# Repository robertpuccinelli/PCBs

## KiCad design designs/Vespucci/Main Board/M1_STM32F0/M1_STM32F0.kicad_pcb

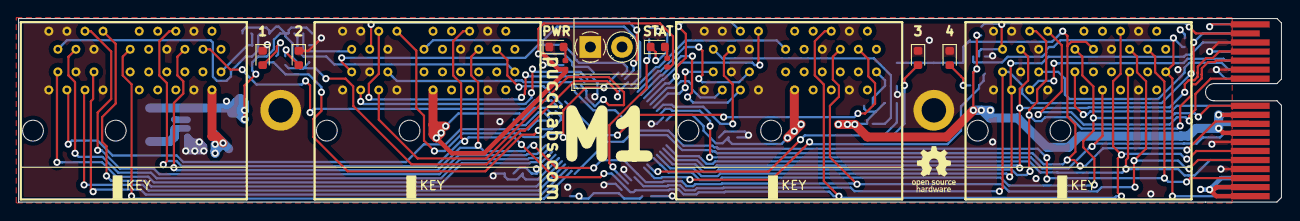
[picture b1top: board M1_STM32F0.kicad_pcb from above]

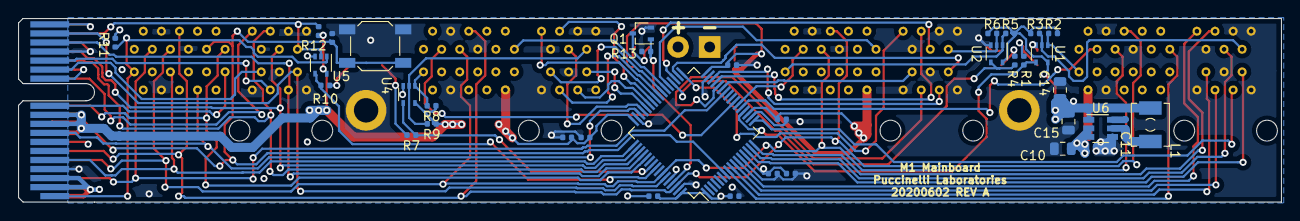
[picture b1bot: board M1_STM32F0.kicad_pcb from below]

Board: 4 copper layers, 139.7 x 20.3 mm, 52 parts (35 on the bottom side), 67 nets.

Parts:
C1, C3, C4, C5, C6, C7, C9, C11: 100nF; C_0402_1005Metric
C2, C8: 4.7uF; C_0402_1005Metric
C10: 4.7uF; C_0805_2012Metric
C14, C15: 22uF; C_0805_2012Metric
D1, D2, D3, D4, D5, D6: LED; LED_0603_1608Metric
G1: OSHW_logo
H1, H2: MountingHole_Pad; MountingHole_2.7mm_M2.5_ISO7380_Pad
J1, J2, J3, J5: PCIe Connector; UMAX_3091-10100T_PCIe_x1
J6: PCIe Card Edge; BUS_PCIexpress_x1
J7: Screw_Terminal_01x02; TerminalBlock_Phoenix_PT-1,5-2-3.5-H_1x02_P3.50mm_Horizontal
L1: 3.3uH; MS0420
Q1: BSS138W; SOT-323_SC-70
R1, R4, R7, R10, R14, R15: 470R; R_0402_1005Metric
R2, R3, R5, R6, R8, R9, R11, R12: 9K53; R_0402_1005Metric
R13: 51K; R_0402_1005Metric
SW1: SW_Push; SW_SPST_SKQG_WithoutStem
U1, U2, U4, U5: NL17SZ00; SOT-353_SC-70-5
U3: STM32F070RBTx; LQFP-64_10x10mm_P0.5mm
U6: AP6320x; TSOT-23-6

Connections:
+BATT: C10.1, J1.a2, J1.a3, J1.b1, J1.b2, J2.a2, J2.a3, J2.b1, J2.b2, J3.a2, J3.a3, J3.b1, J3.b2, J5.a2, J5.a3, J5.b1, J5.b2, J6.a2, J6.a3, J6.b1, J6.b2, J7.1, U6.2, U6.3
/ADC_IN5: J1.b3, U3.21
/ADC_IN6: J2.b3, U3.22
/ADC_IN7: J3.b3, U3.23
/ADC_IN8: J5.b3, J6.b3, U3.26
/I2C1_SCL: J1.b5, J2.b5, J3.b5, J5.b5, J6.b5, U3.58
/I2C1_SDA: J1.b6, J2.b6, J3.b6, J5.b6, J6.b6, U3.62
/PRSNT1: R1.1, U1.4, U3.20
/PRSNT1A: J1.a1, R2.2, U1.1
/PRSNT1B: J1.b17, R3.2, U1.2
/PRSNT2: R4.1, U2.4, U3.36
/PRSNT2A: J2.a1, R5.2, U2.1
/PRSNT2B: J2.b17, R6.2, U2.2
/PRSNT3: R7.1, U3.55, U4.4
/PRSNT3A: J3.a1, R8.2, U4.1
/PRSNT3B: J3.b17, R9.2, U4.2
/PRSNT4: R10.1, U3.56, U5.4
/PRSNT4A: J5.a1, J6.a1, R11.2, U5.1
/PRSNT4B: J5.b17, J6.b17, R12.2, U5.2
/PWROK4: J5.a11, J6.a11
/RST: C1.1, J5.b9, J6.b9, SW1.2, U3.7
/STATUS: Q1.1, R13.1, U3.61
/SWCLK: J5.a5, J6.a5, U3.49
/SWDIO: J5.a8, J6.a8, U3.46
/SW_PWR1: J1.b11, U3.8
/SW_PWR2: J2.b11, U3.37
/SW_PWR3: J3.b11, U3.38
/SW_PWR4: J5.b11, J6.b11, U3.53
/USART1_CTS: J3.a17, U3.44
/USART1_DCD: J3.a14, U3.40
/USART1_DTR: J3.a13, U3.39
/USART1_RI: J3.b12, U3.41
/USART1_RTS: J3.b15, U3.45
/USART1_RX: J3.a16, U3.43
/USART1_TX: J3.b14, U3.42
/USART2_CTS: J1.a17, U3.14
/USART2_DCD: J1.a14, U3.10
/USART2_DTR: J1.a13, U3.9
/USART2_RI: J1.b12, U3.11
/USART2_RTS: J1.b15, U3.15
/USART2_RX: J1.a16, U3.17
/USART2_TX: J1.b14, U3.16
/USART3_CTS: J2.a17, U3.34
/USART3_DCD: J2.a14, U3.28
/USART3_DTR: J2.a13, U3.27
/USART3_RI: J2.b12, U3.33
/USART3_RTS: J2.b15, U3.35
/USART3_RX: J2.a16, U3.30
/USART3_TX: J2.b14, U3.29
/USART4_CTS: J5.a17, J6.a17, U3.59
/USART4_DCD: J5.a14, J6.a14
/USART4_DTR: J5.a13, J6.a13
/USART4_RI: J5.b12, J6.b12
/USART4_RTS: J5.b15, J6.b15, U3.50
/USART4_RX: J5.a16, J6.a16, U3.52
/USART4_TX: J5.b14, J6.b14, U3.51
GND: C1.2, C2.1, C3.1, C4.1, C5.1, C6.1, C7.1, C8.1, C9.1, C10.2, C14.2, C15.2, D1.1, D2.1, D3.1, D4.1, D6.1, H1.1, H2.1, J1.a4, J1.a12, J1.a15, J1.a18, J1.b4, J1.b7, J1.b13, J1.b16, J1.b18, J2.a4, J2.a12, J2.a15, J2.a18, J2.b4, J2.b7, J2.b13, J2.b16, J2.b18, J3.a4, J3.a12, J3.a15, J3.a18, J3.b4, J3.b7, J3.b13, J3.b16, J3.b18, J5.a4, J5.a12, J5.a15, J5.a18, J5.b4, J5.b7, J5.b13, J5.b16, J5.b18, J6.a4, J6.a12, J6.a15, J6.a18, J6.b4, J6.b7, J6.b13, J6.b16, J6.b18, J7.2, Q1.2, R13.2, SW1.1, U1.3, U2.3, U3.12, U3.18, U3.31, U3.47, U3.60, U3.63, U4.3, U5.3, U6.4
unnamed: C11.1, U6.6
unnamed: C11.2, L1.1, U6.5
unnamed: D1.2, R1.2
unnamed: D2.2, R4.2
unnamed: D3.2, R7.2
unnamed: D4.2, R10.2
unnamed: D5.1, Q1.3
unnamed: D5.2, R14.2
unnamed: D6.2, R15.1
VBUS: C2.2, C3.2, C4.2, C5.2, C6.2, C7.2, C8.2, C9.2, C14.1, C15.1, J1.a9, J1.a10, J1.b8, J1.b10, J2.a9, J2.a10, J2.b8, J2.b10, J3.a9, J3.a10, J3.b8, J3.b10, J5.a9, J5.a10, J5.b8, J5.b10, J6.a9, J6.a10, J6.b8, J6.b10, L1.2, R2.1, R3.1, R5.1, R6.1, R8.1, R9.1, R11.1, R12.1, R14.1, R15.2, U1.5, U2.5, U3.1, U3.13, U3.19, U3.32, U3.48, U3.64, U4.5, U5.5, U6.1

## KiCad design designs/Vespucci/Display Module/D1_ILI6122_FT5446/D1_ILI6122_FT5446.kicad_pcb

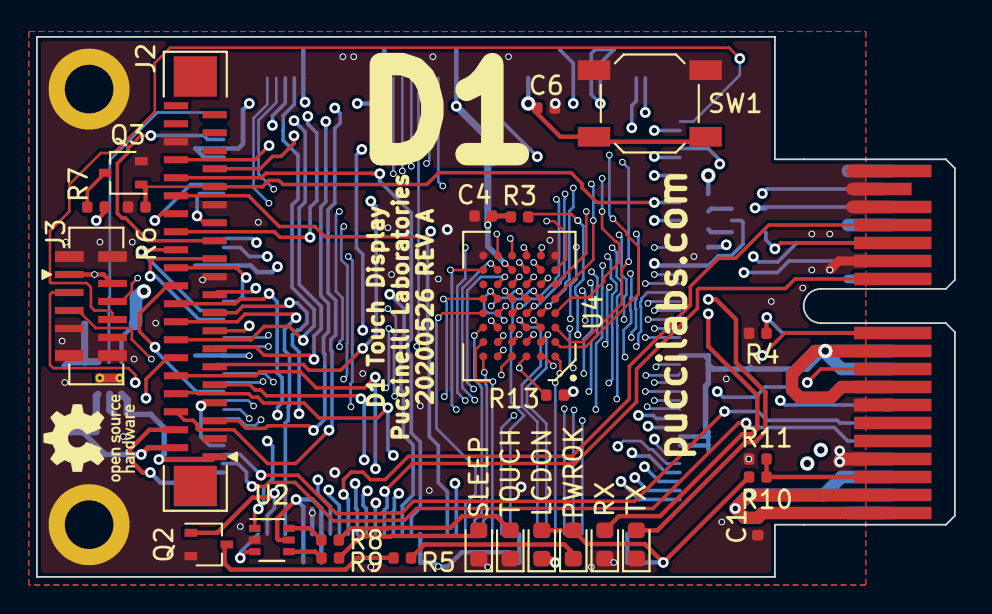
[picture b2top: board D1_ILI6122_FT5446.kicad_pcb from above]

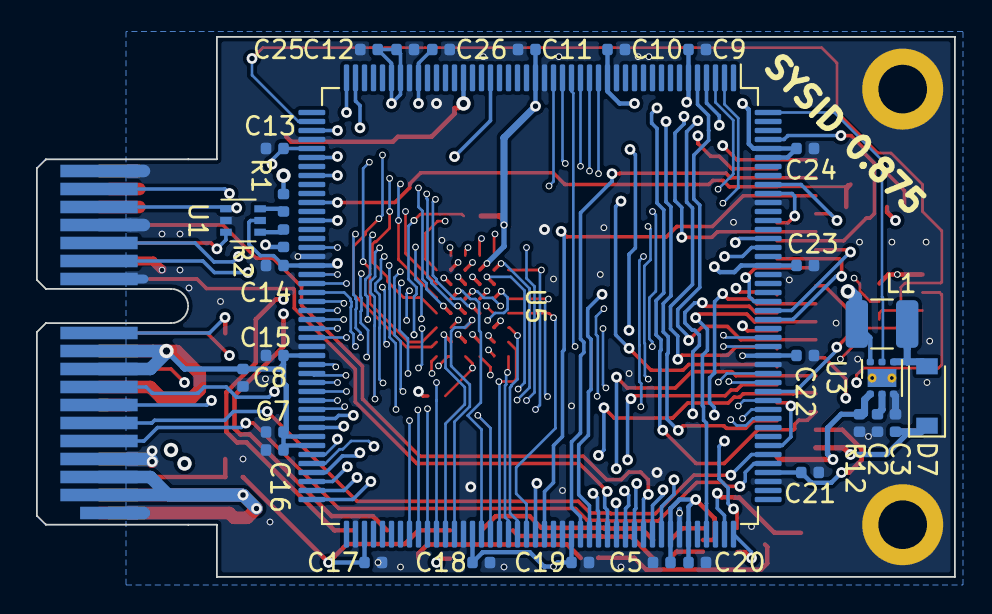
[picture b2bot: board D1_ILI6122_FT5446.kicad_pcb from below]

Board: 4 copper layers, 51.0 x 30.0 mm, 61 parts (31 on the bottom side), 111 nets.

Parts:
C1, C3: 4.7uF; C_0402_1005Metric
C2: 220nF; C_0402_1005Metric
C4, C26: 1uF; C_0402_1005Metric
C5, C7: 2.2uF; C_0402_1005Metric
C6, C9, C10, C11, C12, C13, C14, C15, C16, C17, C18, C19, C20, C21, C22, C23, C24, C25: 100nF; C_0402_1005Metric
C8: 10uF; C_0402_1005Metric
D1, D2, D3, D4, D5, D6: LED; LED_0603_1608Metric
D7: MBR0540; D_SOD-123
G1: OSHW_logo
H1, H2: MountingHole_Pad; MountingHole_2.7mm_M2.5_ISO7380_Pad
J1: PCIExpress; BUS_PCIexpress_x1
J2: FFC_ILI6122; JUSHUO_AFC11_S40IC
J3: FFC_FT5446; Amphenol_62674-08
L1: 10uH; L_1210_3225Metric
Q2, Q3: BSS138W; SOT-323_SC-70
R1, R2, R5, R7, R8, R9: 470R; R_0402_1005Metric
R3, R13: 39K; R_0402_1005Metric
R4, R6: 51K; R_0402_1005Metric
R10: 1K2; R_0402_1005Metric
R11: 8K41; R_0402_1005Metric
R12: 2R4; R_0402_1005Metric
SW1: SW_Push; SW_SPST_SKQG_WithoutStem
U1, U2: NC7WZ14; SOT-363_SC-70-6
U3: TPS61165DRV; WSON-6-1EP_2x2mm_P0.65mm_EP1x1.6mm_ThermalVias
U4: SST39VF3201C-70-4I-B3KE; TFBGA-48_6x8_6.0x8.0mm
U5: STM32F429IGTx; LQFP-176_24x24mm_P0.5mm

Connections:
+3V3: C4.2, C5.1, C7.2, C8.2, C9.2, C10.2, C11.2, C12.2, C13.2, C14.2, C15.2, C16.2, C17.2, C18.2, C19.2, C20.2, C21.2, C22.2, C23.2, C24.2, C25.2, C26.2, D3.2, D4.2, J1.a9, J1.a10, J1.b8, J1.b10, J2.4, J3.1, J3.2, R3.1, R10.1, R13.1, U1.5, U2.5, U4.G4, U5.6, U5.15, U5.23, U5.36, U5.38, U5.39, U5.49, U5.62, U5.72, U5.81, U5.82, U5.91, U5.103, U5.114, U5.125, U5.127, U5.136, U5.149, U5.159, U5.171, U5.172
+BATT: C1.2, J1.a2, J1.a3, J1.b1, J1.b2, L1.1, U3.6
/D1_DisplayInterface/LCD_B1: J2.22, U5.155
/D1_DisplayInterface/LCD_B2: J2.23, U5.153
/D1_DisplayInterface/LCD_B3: J2.24, U5.154
/D1_DisplayInterface/LCD_B4: J2.25, U5.173
/D1_DisplayInterface/LCD_B5: J2.26, U5.47
/D1_DisplayInterface/LCD_B6: J2.27, U5.167
/D1_DisplayInterface/LCD_B7: J2.28, U5.168
/D1_DisplayInterface/LCD_CLK: J2.30, U5.111
/D1_DisplayInterface/LCD_DE: J2.34, U5.28
/D1_DisplayInterface/LCD_G0: J2.13, U5.4
/D1_DisplayInterface/LCD_G1: J2.14, U5.5
/D1_DisplayInterface/LCD_G2: J2.15, U5.52
/D1_DisplayInterface/LCD_G3: J2.16, U5.129
/D1_DisplayInterface/LCD_G4: J2.17, U5.79
/D1_DisplayInterface/LCD_G5: J2.18, U5.80
/D1_DisplayInterface/LCD_G6: J2.19, U5.116
/D1_DisplayInterface/LCD_G7: J2.20, U5.145
/D1_DisplayInterface/LCD_HSYNC: J2.32, U5.115
/D1_DisplayInterface/LCD_PWM: U3.5, U5.176
/D1_DisplayInterface/LCD_R0: J2.5, U5.43
/D1_DisplayInterface/LCD_R1: J2.6, U5.44
/D1_DisplayInterface/LCD_R2: J2.7, U5.139
/D1_DisplayInterface/LCD_R3: J2.8, U5.86
/D1_DisplayInterface/LCD_R4: J2.9, U5.87
/D1_DisplayInterface/LCD_R5: J2.10, U5.88
/D1_DisplayInterface/LCD_R6: J2.11, U5.57
/D1_DisplayInterface/LCD_R7: J2.12, U5.110
/D1_DisplayInterface/LCD_VSYNC: J2.33, U5.50
/D1_DisplayInterface/LED+: C3.1, D7.1, J2.2
/D1_DisplayInterface/LED-: J2.1, R12.2, U3.1
/D1_DisplayInterface/~TP_RST: J3.6, U5.46
/D1_SST39VF3201C/A0: U4.E1, U5.16
/D1_SST39VF3201C/A1: U4.D1, U5.17
/D1_SST39VF3201C/A2: U4.C1, U5.18
/D1_SST39VF3201C/A3: U4.A1, U5.19
/D1_SST39VF3201C/A4: U4.B1, U5.20
/D1_SST39VF3201C/A5: U4.D2, U5.21
/D1_SST39VF3201C/A6: U4.C2, U5.60
/D1_SST39VF3201C/A7: U4.A2, U5.63
/D1_SST39VF3201C/A8: U4.B5, U5.64
/D1_SST39VF3201C/A9: U4.A5, U5.65
/D1_SST39VF3201C/A10: U4.C5, U5.66
/D1_SST39VF3201C/A11: U4.D5, U5.67
/D1_SST39VF3201C/A12: U4.B6, U5.106
/D1_SST39VF3201C/A13: U4.A6, U5.107
/D1_SST39VF3201C/A14: U4.C6, U5.108
/D1_SST39VF3201C/A15: U4.D6, U5.109
/D1_SST39VF3201C/A16: U4.E6, U5.99
/D1_SST39VF3201C/A17: U4.B2, U5.100
/D1_SST39VF3201C/A18: U4.C3, U5.101
/D1_SST39VF3201C/A19: U4.D4, U5.2
/D1_SST39VF3201C/A20: U4.D3, U5.3
/D1_SST39VF3201C/D0: U4.E2, U5.104
/D1_SST39VF3201C/D1: U4.H2, U5.105
/D1_SST39VF3201C/D2: U4.E3, U5.142
/D1_SST39VF3201C/D3: U4.H3, U5.143
/D1_SST39VF3201C/D4: U4.H4, U5.68
/D1_SST39VF3201C/D5: U4.E4, U5.69
/D1_SST39VF3201C/D6: U4.H5, U5.70
/D1_SST39VF3201C/D7: U4.E5, U5.73
/D1_SST39VF3201C/D8: U4.F2, U5.74
/D1_SST39VF3201C/D9: U4.G2, U5.75
/D1_SST39VF3201C/D10: U4.F3, U5.76
/D1_SST39VF3201C/D11: U4.G3, U5.77
/D1_SST39VF3201C/D12: U4.F4, U5.78
/D1_SST39VF3201C/D13: U4.G5, U5.96
/D1_SST39VF3201C/D14: U4.F5, U5.97
/D1_SST39VF3201C/D15: U4.G6, U5.98
/D1_STM32F429/FMC_RST: U4.B4, U5.144
/D1_STM32F429/FMC_nE1: U4.F1, U5.151
/D1_STM32F429/FMC_nOE: U4.G1, U5.146
/D1_STM32F429/FMC_nWAIT: R13.2, U4.A3, U5.150
/D1_STM32F429/FMC_nWE: U4.A4, U5.147
/D1_STM32F429/I2C_SCL: J3.3, U5.85
/D1_STM32F429/I2C_SDA: J3.4, U5.84
/D1_STM32F429/RST: C6.1, SW1.2, U5.31
/LCD_ON: J2.31, Q3.1, R6.1, U5.55
/PWROK: J1.a11, Q2.1, R4.1, U5.131
/SYSID: J1.b3, R10.2, R11.2
/TCK: J1.a5, U5.137
/TDI: J1.a6, U5.138
/TDO: J1.a7, U5.161
/TMS: J1.a8, U5.124
/hCTS: J1.a17, U5.123
/hDCD: J1.a14, U5.117
/hDTR: J1.a13, U5.119
/hRI: J1.b12, U5.118
/hRTS: J1.b15, U5.122
/hRX: J1.a16, U1.1, U5.120
/hTX: J1.b14, U1.3, U5.121
/~SLEEP: J1.b11, U2.3, U5.132
/~TP_INT: J3.5, U2.1, U5.83
/~TRST: J1.b9, U5.162
GND: C1.1, C2.2, C3.2, C4.1, C5.2, C6.2, C7.1, C8.1, C9.1, C10.1, C11.1, C12.1, C13.1, C14.1, C15.1, C16.1, C17.1, C18.1, C19.1, C20.1, C21.1, C22.1, C23.1, C24.1, C25.1, C26.1, D1.1, D2.1, D5.1, D6.1, H1.1, H2.1, J1.a1, J1.a4, J1.a12, J1.a15, J1.a18, J1.b4, J1.b7, J1.b13, J1.b16, J1.b17, J1.b18, J2.3, J2.21, J2.29, J2.36, J3.7, J3.8, J3.GND, Q2.2, Q3.2, R4.2, R6.2, R11.1, R12.1, SW1.1, U1.2, U2.2, U3.3, U4.H1, U4.H6, U5.14, U5.22, U5.37, U5.48, U5.61, U5.71, U5.90, U5.102, U5.113, U5.126, U5.135, U5.148, U5.158, U5.166
unnamed: C2.1, U3.2
unnamed: D1.2, R1.1
unnamed: D2.2, R2.1
unnamed: D3.1, R5.2
unnamed: D4.1, R7.2
unnamed: D5.2, R8.1
unnamed: D6.2, R9.1
unnamed: D7.2, L1.2, U3.4
unnamed: Q2.3, R5.1
unnamed: Q3.3, R7.1
unnamed: R1.2, U1.6
unnamed: R2.2, U1.4
unnamed: R3.2, U4.B3
unnamed: R8.2, U2.6
unnamed: R9.2, U2.4

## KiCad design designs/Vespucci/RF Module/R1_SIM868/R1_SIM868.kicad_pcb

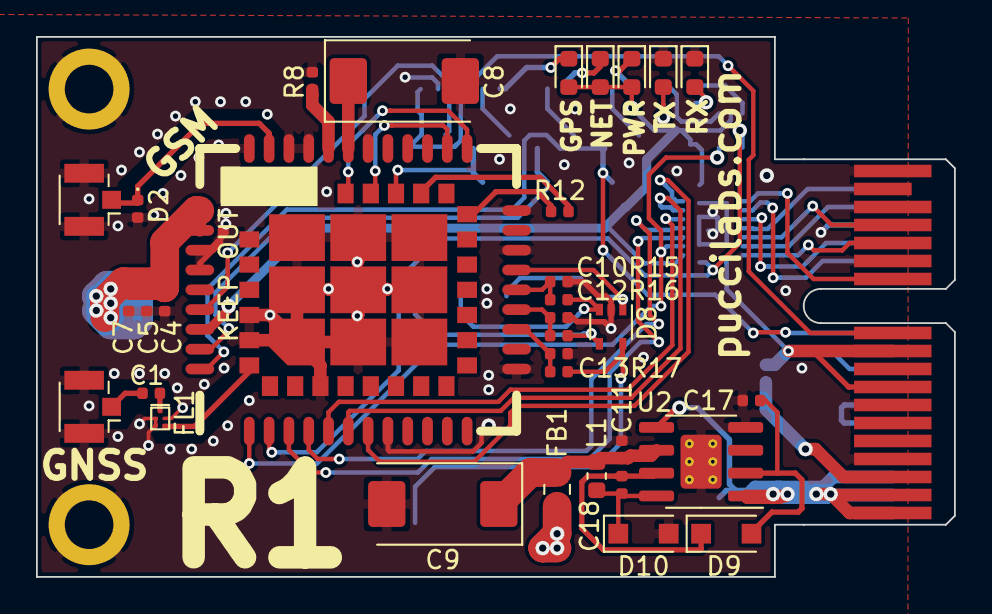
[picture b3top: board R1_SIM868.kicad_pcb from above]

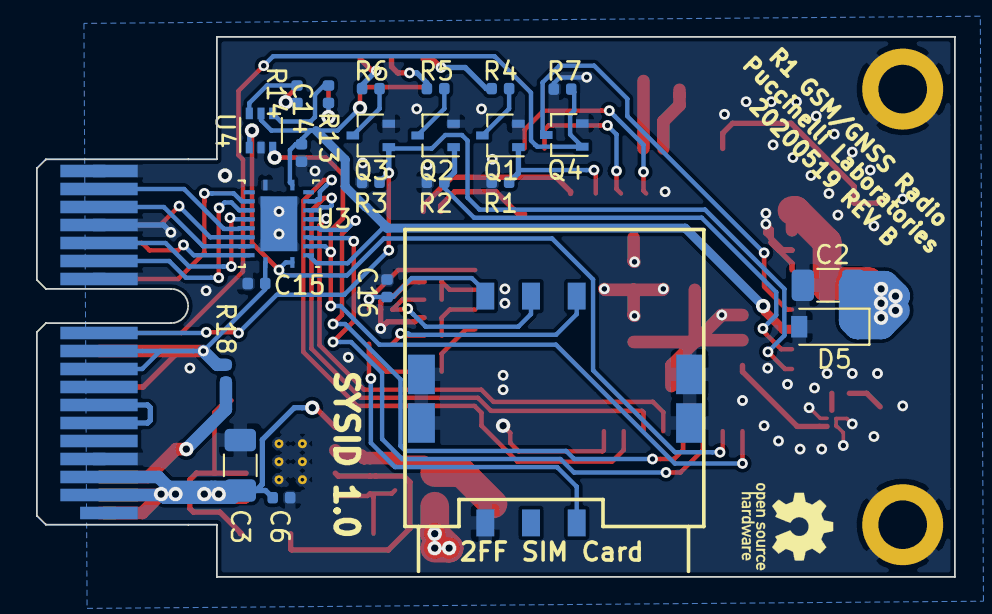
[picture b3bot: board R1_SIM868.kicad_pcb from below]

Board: 4 copper layers, 51.0 x 30.0 mm, 61 parts (25 on the bottom side), 57 nets.

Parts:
C1: 27pF; C_0402_1005Metric
C2, C3: 100uF; C_1206_3216Metric
C4, C6: 1uF; C_0402_1005Metric
C5: 47pF; C_0402_1005Metric
C7, C10, C12, C13: 22pF; C_0402_1005Metric
C8, C9: 330uF; CP_EIA-7343-31_Kemet-D
C11, C14, C15, C16, C17, C18: 100nF; C_0402_1005Metric
D1, D3, D4, D6, D7: LED; LED_0603_1608Metric
D2: D_TVS; D_0402_1005Metric
D5: 5V1 500mW; D_SOD-123
D8: ESDA6V1W5; SOT-353_SC-70-5
D9, D10: D; D_SOD-123F
FB1: 250R; L_0805_2012Metric
FL1: SAFFB1G56KB0F0A; Filter_1109-5_1.1x0.9mm
G1: OSHW_logo
H1, H2: MountingHole_Pad; MountingHole_2.7mm_M2.5_ISO7380_Pad
J1, J2: U.FL IPEX; U.FL_Hirose_U.FL-R-SMT-1_Vertical
J3: SIM_Card; SIM-104
J4: PCIExpress; BUS_PCIexpress_x1
L1: 2.2uH; L_0603_1608Metric
Q1, Q2, Q3, Q4: BSS138W; SOT-323_SC-70
R1, R2, R3, R7: 51K; R_0402_1005Metric
R4, R5, R6, R13, R14: 470R; R_0402_1005Metric
R8, R12, R18: 9K53; R_0402_1005Metric
R15, R16, R17: 51R; R_0402_1005Metric
U1: SIM868
U2: NCV891330; SOIC-8-1EP_3.9x4.9mm_P1.27mm_EP2.29x3mm_ThermalVias
U3: TXS0108ERGY; VQFN-20_EP_3.5x4.5_Pitch0.5mm
U4: NC7WZ14; SOT-363_SC-70-6

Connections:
+BATT: C3.1, C6.1, J4.a2, J4.a3, J4.b1, J4.b2, U2.1, U2.5
/ANT_GNSS: FL1.4, U1.68
/ANT_GSM: D2.1, J2.1, U1.32
/GPS_EN: R12.1, U1.57
/GPS_PPS: Q1.1, R1.1, U1.60
/GPS_RX: U1.22, U1.62
/GPS_TX: U1.23, U1.61
/NETACT: Q2.1, R2.1, U1.41
/PWROK: J4.a11, Q3.1, R3.1, U1.42
/SIM_CLK: C12.1, R16.2, U1.16
/SIM_DATA: C13.1, R17.2, U1.15
/SIM_RST: C10.1, R15.2, U1.17
/SIM_VDD: C16.2, D8.1, J3.1, U1.18
/SW_PWR: J4.b11, Q4.1, R7.1
/SYSID: J4.b3, R18.2
/TDI: J4.a6, J4.a7
/dCTS: U1.4, U3.5
/dDCD: U1.5, U3.6
/dDTR: U1.6, U3.7
/dRI: U1.7, U3.8
/dRTS: U1.3, U3.4
/dRX: U1.2, U3.1, U4.1
/dTX: U1.1, U3.3, U4.3
/hCTS: J4.a17, U3.16
/hDCD: J4.a14, U3.15
/hDTR: J4.a13, U3.14
/hRI: J4.b12, U3.13
/hRTS: J4.b15, U3.17
/hRX: J4.a16, U3.18
/hTX: J4.b14, U3.19
GND: C2.2, C3.2, C4.2, C5.2, C6.2, C7.2, C8.2, C9.2, C10.2, C11.2, C12.2, C13.2, C14.2, C15.2, C16.1, C17.2, D2.2, D5.2, D6.1, D7.1, D8.2, D10.2, FL1.2, FL1.3, FL1.5, H1.1, H2.1, J1.2, J2.2, J3.5, J4.a1, J4.a4, J4.a12, J4.a15, J4.a18, J4.b4, J4.b7, J4.b13, J4.b16, J4.b17, J4.b18, Q1.2, Q2.2, Q3.2, Q4.2, R1.2, R2.2, R3.2, R7.2, R8.1, U1.8, U1.13, U1.19, U1.21, U1.27, U1.30, U1.31, U1.33, U1.36, U1.37, U1.45, U1.63, U1.66, U1.67, U1.69, U1.70, U1.71, U1.72, U1.73, U1.74, U1.75, U1.76, U1.77, U2.4, U2.9, U3.11, U3.21, U4.2
unnamed: C1.1, FL1.1
unnamed: C1.2, J1.1
unnamed: C8.1, U1.28
unnamed: C9.1, C11.1, FB1.2, L1.2, U2.6
unnamed: C17.1, D9.2, U2.2
unnamed: C18.1, D10.1, L1.1, U2.8
unnamed: C18.2, D9.1, U2.7
unnamed: D1.1, R4.2
unnamed: D3.1, R5.2
unnamed: D4.1, R6.2
unnamed: D6.2, R13.1
unnamed: D7.2, R14.1
unnamed: D8.3, J3.2, R15.1
unnamed: D8.4, J3.3, R16.1
unnamed: D8.5, J3.7, R17.1
unnamed: Q1.3, R4.1
unnamed: Q2.3, R5.1
unnamed: Q3.3, R6.1
unnamed: Q4.3, U1.39
unnamed: R8.2, U1.29
unnamed: R12.2, U1.59
unnamed: R13.2, U4.4
unnamed: R14.2, U4.6
VBUS: C15.1, J4.a9, J4.a10, J4.b8, J4.b10, R18.1, U3.20
VCC: C14.1, D1.2, D3.2, D4.2, U1.40, U3.2, U3.10, U4.5
VDD: C2.1, C4.1, C5.1, C7.1, D5.1, FB1.1, U1.34, U1.35

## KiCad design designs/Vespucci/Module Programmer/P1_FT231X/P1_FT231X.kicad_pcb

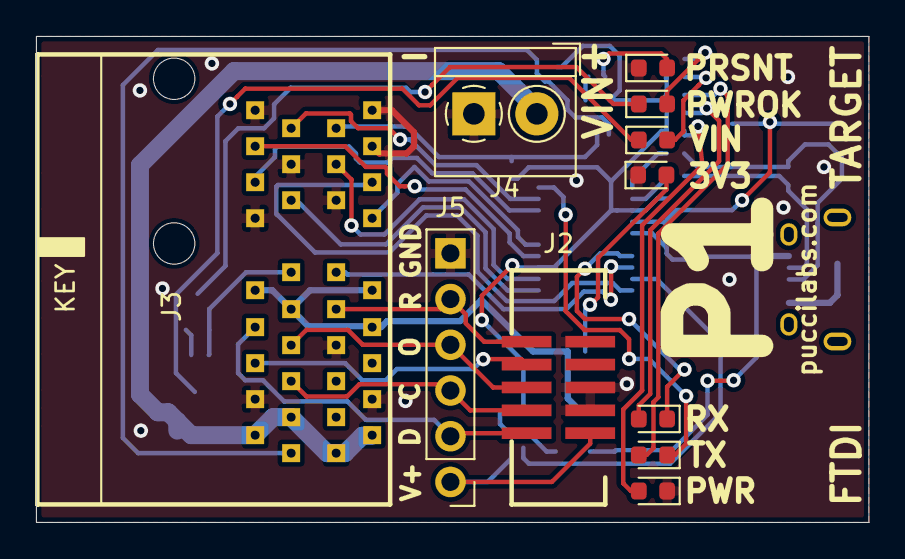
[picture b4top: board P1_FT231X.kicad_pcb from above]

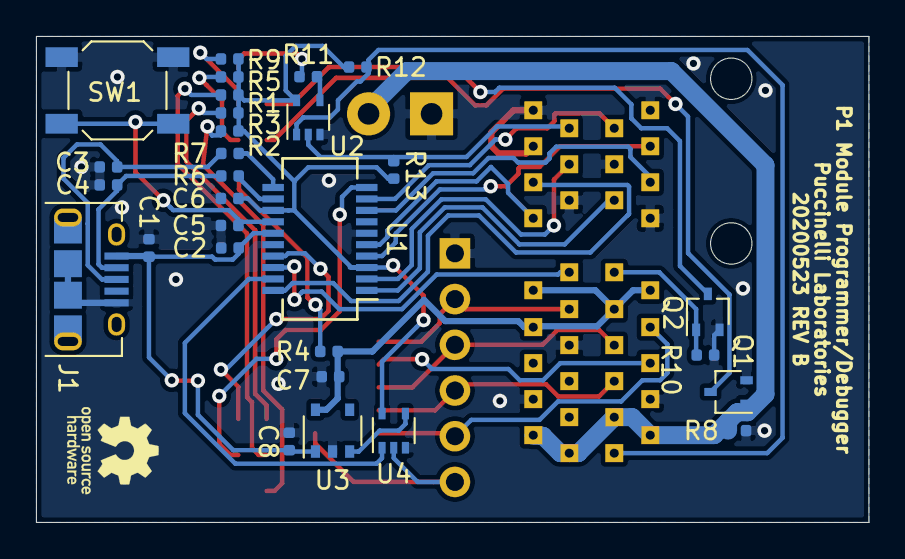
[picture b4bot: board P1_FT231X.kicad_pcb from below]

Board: 2 copper layers, 46.2 x 27.0 mm, 41 parts (30 on the bottom side), 41 nets.

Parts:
C1: 4.7uF; C_0402_1005Metric
C2, C5, C6: 100nF; C_0402_1005Metric
C3, C4: 47pF; C_0402_1005Metric
C7, C8: 1uF; C_0402_1005Metric
D1, D2, D3, D4, D5, D6, D7: LED; LED_0603_1608Metric
G1: OSHW_logo
J1: USB_B_Micro; USB_Micro-B_Amphenol_10118194-0001LF
J2: JTAG Connector; Shroud_2x05_P1.27mm_Verticle
J3: PCIe Connector; UMAX_3091-10100T_PCIe_x1
J4: Screw_VIn; TerminalBlock_4Ucon_1x02_P3.50mm_Horizontal
J5: SWD Header; PinHeader_1x06_P2.54mm_Vertical
Q1, Q2: BSS138W; SOT-323_SC-70
R1, R2, R3, R4, R5, R9, R11: 470R; R_0402_1005Metric
R6, R7: 27R; R_0402_1005Metric
R8, R10: 51K; R_0402_1005Metric
R12, R13: 9K53; R_0402_1005Metric
SW1: SW_RST; SW_SPST_SKQG_WithStem
U1: FT231XS; SSOP-20_3.9x8.7mm_P0.635mm
U2: NL17SZ00; SOT-353_SC-70-5
U3: NCP703xN33T; TSOP-5_1.65x3.05mm_P0.95mm
U4: NL17SZ32; SOT-353_SC-70-5

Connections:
+3V3: C6.2, R1.1, R2.1, R3.1, R5.1, R9.1, R12.1, R13.1, U1.3, U1.13, U2.5, U4.5
+5V: C1.1, C2.1, C8.1, J1.1, U1.15, U3.1
+BATT: J3.a2, J3.a3, J3.b1, J3.b2, J4.1, Q1.1, R8.1
/LED_RX: D3.1, U1.17
/LED_TX: D1.1, U1.10
/PRSNT1: J3.a1, R12.2, U2.1
/PRSNT2: J3.b17, R13.2, U2.2
/PWR1: U1.19, U4.1
/PWR2: J2.1, J5.1, U4.2
/PWR_OK: J3.a11, Q2.1, R10.1
/SW_PWR: J3.b11, U1.18
/TCLK: J2.4, J3.a5, J5.3
/TDI: J2.8, J3.a6
/TDO: J2.6, J3.a7, J5.4
/TMS: J2.2, J3.a8, J5.2
/TRST: J2.10, J3.b9, J5.5
/hCTS: J3.a17, U1.9
/hDCD: J3.a14, U1.8
/hDTR: J3.a13, U1.1
/hRI: J3.b12, U1.5
/hRTS: J3.b15, U1.2
/hRX: J3.a16, U1.4
/hTX: J3.b14, U1.20
GND: C1.2, C2.2, C3.2, C4.2, C5.2, C6.1, C7.2, C8.2, D2.1, D4.1, D7.1, J1.5, J1.6, J2.3, J2.5, J2.9, J3.a4, J3.a12, J3.a15, J3.a18, J3.b4, J3.b7, J3.b13, J3.b16, J3.b18, J4.2, J5.6, Q1.2, Q2.2, R8.2, R10.2, SW1.1, U1.6, U1.16, U2.3, U3.2, U4.3
unnamed: C3.1, J1.3, R7.2
unnamed: C4.1, J1.2, R6.2
unnamed: C5.1, SW1.2, U1.14
unnamed: D1.2, R1.2
unnamed: D2.2, R2.2
unnamed: D3.2, R3.2
unnamed: D4.2, R4.2
unnamed: D5.1, Q1.3
unnamed: D5.2, R5.2
unnamed: D6.1, Q2.3
unnamed: D6.2, R9.2
unnamed: D7.2, R11.2
unnamed: R6.1, U1.12
unnamed: R7.1, U1.11
unnamed: R11.1, U2.4
unnamed: U3.3, U4.4
VBUS: C7.1, J3.a9, J3.a10, J3.b8, J3.b10, R4.1, U3.5

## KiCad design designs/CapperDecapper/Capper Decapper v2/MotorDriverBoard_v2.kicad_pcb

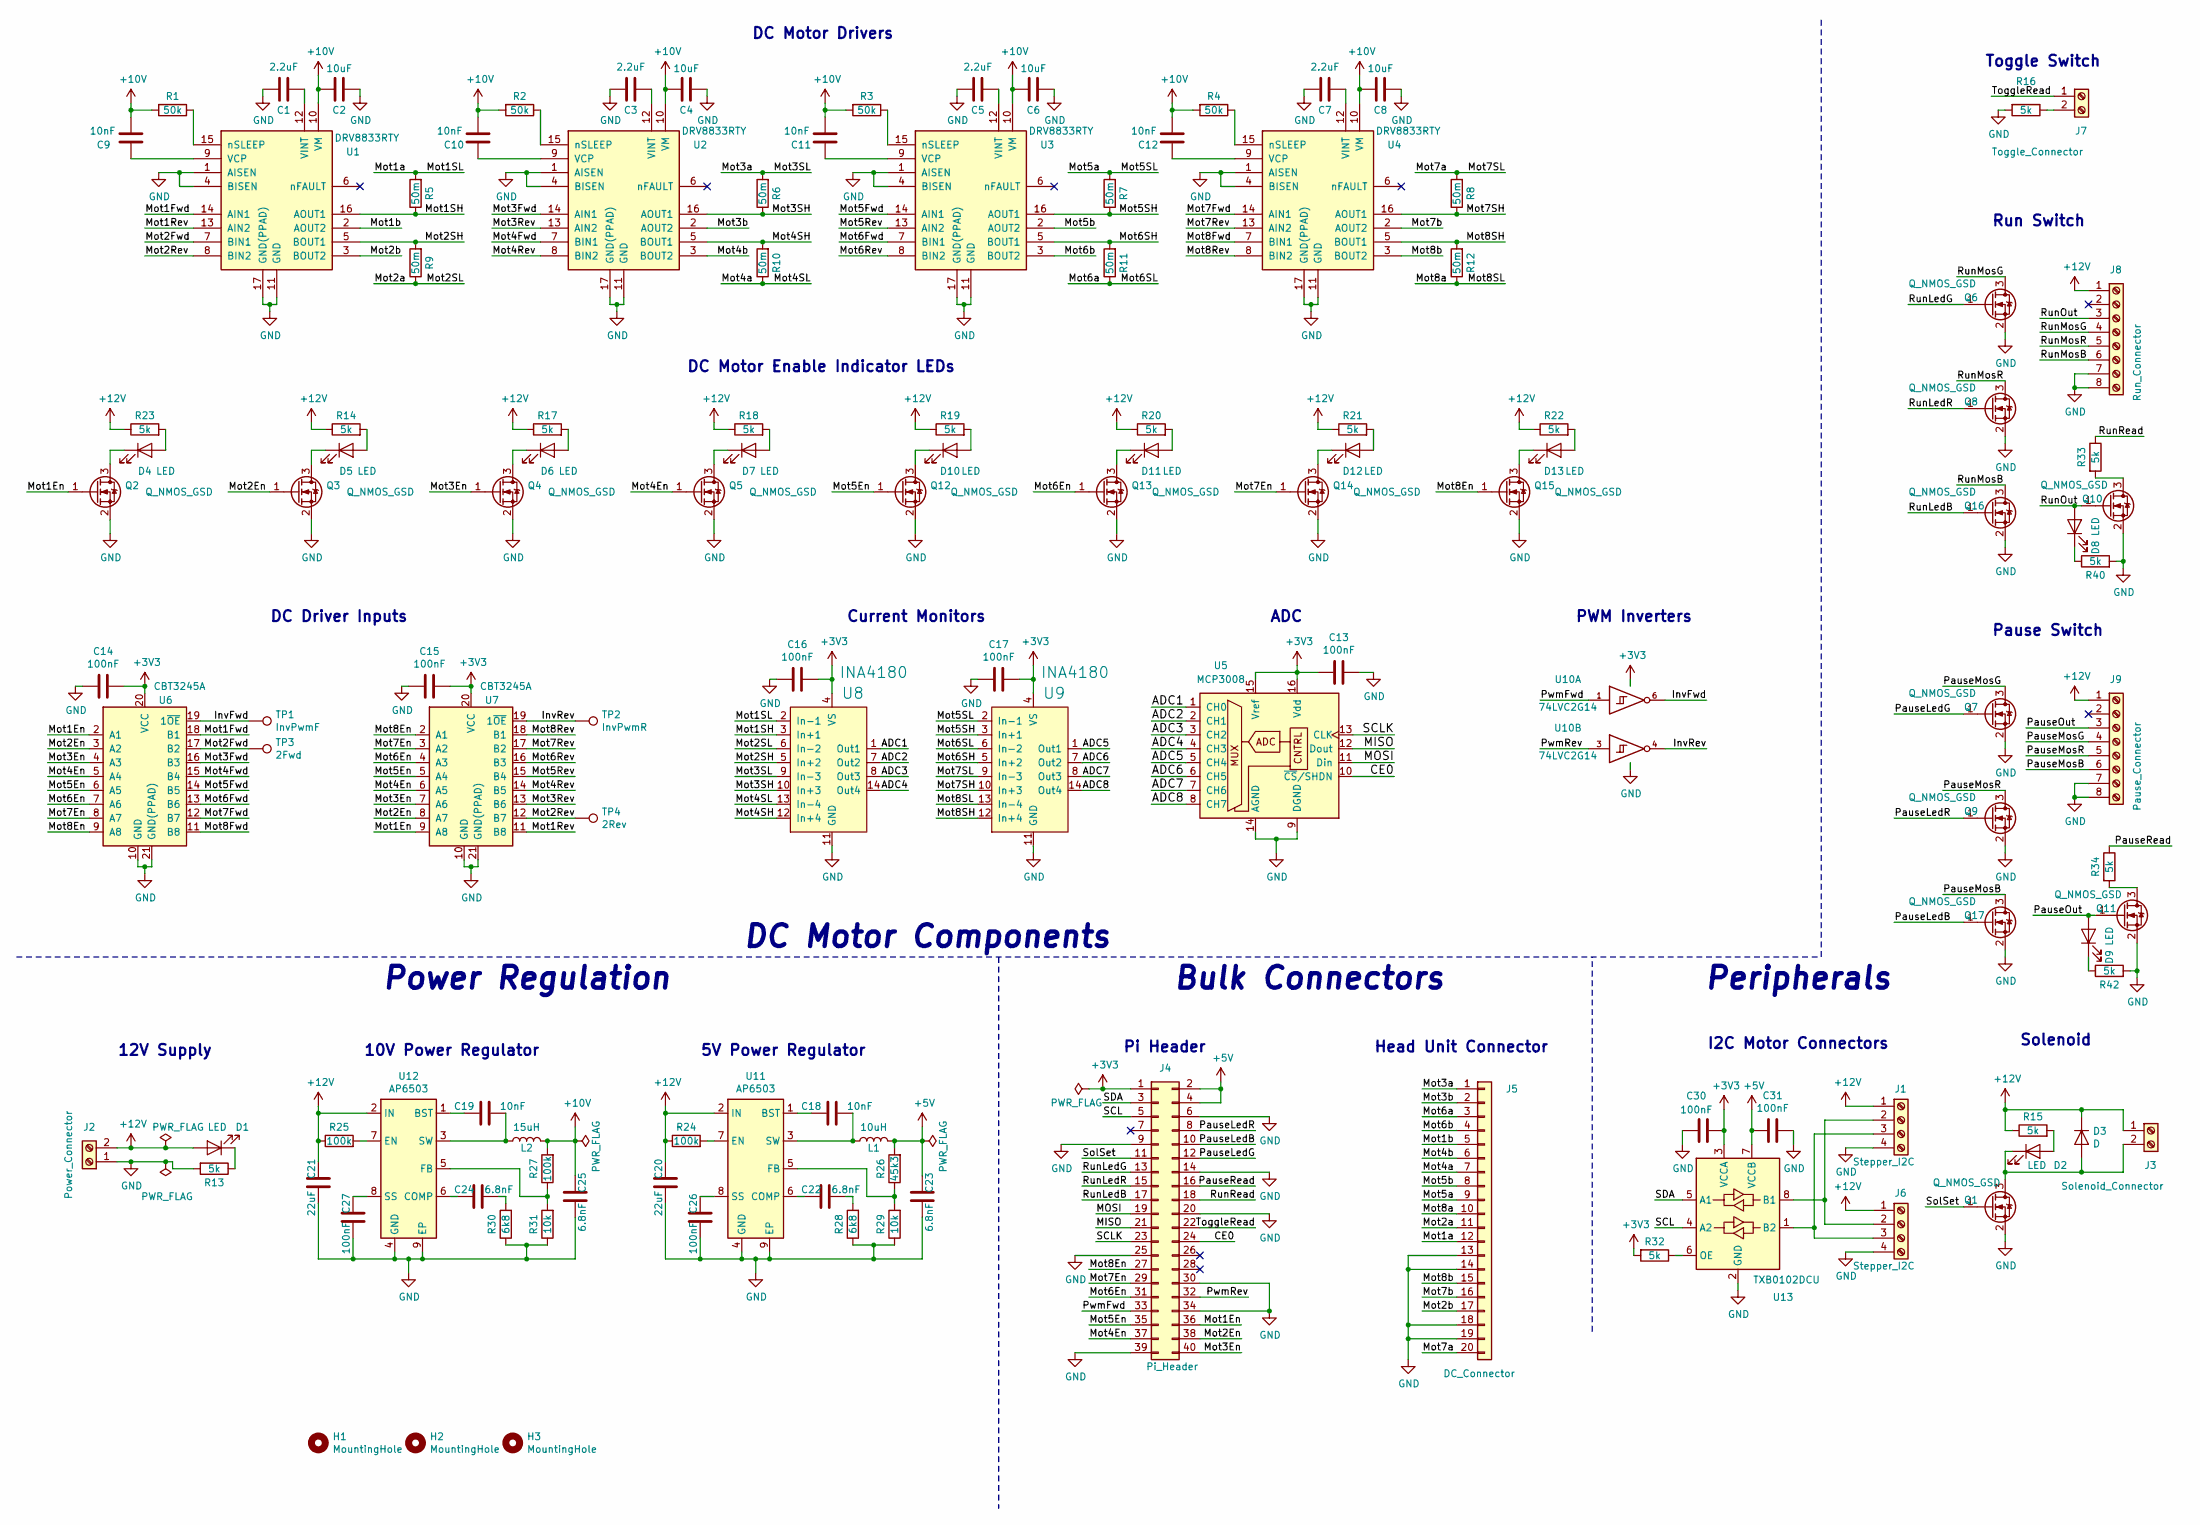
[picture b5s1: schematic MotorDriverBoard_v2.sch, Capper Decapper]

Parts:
C1, C3, C5, C7: 2.2uF; C_0603_1608Metric
C2, C4, C6, C8: 10uF; C_0805_2012Metric
C9, C10, C11, C12, C18, C19: 10nF; C_0603_1608Metric
C13, C14, C15, C16, C17, C26, C27, C30, C31: 100nF; C_0603_1608Metric
C20, C21: 22uF; C_0805_2012Metric
C22, C23, C24, C25: 6.8nF; C_0603_1608Metric
D1, D2, D4, D5, D6, D7, D8, D9, D10, D11, D12, D13: LED; LED_0603_1608Metric
D3: D; D_SOD-123F
H1, H2, H3: MountingHole; MountingHole_2.2mm_M2
J1, J6: Stepper_I2C; TerminalBlock_Phoenix_PT-1,5-4-3.5-H_1x04_P3.50mm_Horizontal
J2: Power_Connector; TerminalBlock_Phoenix_PT-1,5-2-3.5-H_1x02_P3.50mm_Horizontal
J3: Solenoid_Connector; TerminalBlock_Phoenix_PT-1,5-2-3.5-H_1x02_P3.50mm_Horizontal
J4: Pi_Header; PinHeader_2x20_P1.27mm_Vertical
J5: DC_Connector; RP13A-12RC-20PB
J7: Toggle_Connector; TerminalBlock_Phoenix_PT-1,5-2-3.5-H_1x02_P3.50mm_Horizontal
J8: Run_Connector; TerminalBlock_Phoenix_PT-1,5-8-3.5-H_1x08_P3.50mm_Horizontal
J9: Pause_Connector; TerminalBlock_Phoenix_PT-1,5-8-3.5-H_1x08_P3.50mm_Horizontal
L1: 10uH; L_Wuerth_WE-PD-Typ-LS_Handsoldering
L2: 15uH; L_Wuerth_WE-PD-Typ-LS_Handsoldering
Q1, Q2, Q3, Q4, Q5, Q6, Q7, Q8, Q9, Q10, Q11, Q12, Q13, Q14, Q15, Q16, Q17: Q_NMOS_GSD; SOT-23
R1, R2, R3, R4: 50k; R_0603_1608Metric
R5, R6, R7, R8, R9, R10, R11, R12: 50m; R_1206_3216Metric
R13, R14, R15, R16, R17, R18, R19, R20, R21, R22, R23, R32, R33, R34, R40, R42: 5k; R_0603_1608Metric
R24, R25, R27: 100k; R_0603_1608Metric
R26: 45k3; R_0603_1608Metric
R28, R30: 6k8; R_0603_1608Metric
R29, R31: 10k; R_0603_1608Metric
TP1: InvPwmF; TestPoint_Pad_D1.0mm
TP2: InvPwmR; TestPoint_Pad_D1.0mm
TP3: 2Fwd; TestPoint_Pad_D1.0mm
TP4: 2Rev; TestPoint_Pad_D1.0mm
U1, U2, U3, U4: DRV8833RTY; Texas_S-PWQFN-N16_EP2.1x2.1mm_ThermalVias
U5: MCP3008; SOIC-16_3.9x9.9mm_P1.27mm
U6, U7: CBT3245A; WQFN-20-1EP_2.5x4.5mm_P0.5mm_EP1x2.9mm
U8, U9: INA4180; TSSOP-14_4.4x5mm_P0.65mm
U10: 74LVC2G14; SOT-363_SC-70-6
U11, U12: AP6503; Diodes_SO-8EP
U13: TXB0102DCU; VSSOP-8_2.4x2.1mm_P0.5mm

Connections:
+3V3: C13.1, C14.1, C15.1, C16.1, C17.1, C30.1, J4.1, R32.2, U5.15 (Vref), U5.16 (Vdd), U6.20 (VCC), U7.20 (VCC), U8.4 (VS), U9.4 (VS), U10.5 (VCC), U13.3 (VCCA)
+5V: C23.1, C31.2, J4.2, J4.4, L1.2, R26.2, U13.7 (VCCB)
+10V: C2.1, C4.1, C6.1, C8.1, C9.2, C10.2, C11.2, C12.2, C25.1, L2.2, R1.2, R2.2, R3.2, R4.2, R27.2, U1.10 (VM), U2.10 (VM), U3.10 (VM), U4.10 (VM)
+12V: C20.1, C21.1, D1.2 (A), D3.1 (K), J1.1, J2.2, J3.1, J6.1, J8.1, J9.1, R14.1, R15.1, R17.1, R18.1, R19.1, R20.1, R21.1, R22.1, R23.1, R24.1, R25.1, U11.2 (IN), U12.2 (IN)
/ADC1: U5.1 (CH0), U8.1 (Out1)
/ADC2: U5.2 (CH1), U8.7 (Out2)
/ADC3: U5.3 (CH2), U8.8 (Out3)
/ADC4: U5.4 (CH3), U8.14 (Out4)
/ADC5: U5.5 (CH4), U9.1 (Out1)
/ADC6: U5.6 (CH5), U9.7 (Out2)
/ADC7: U5.7 (CH6), U9.8 (Out3)
/ADC8: U5.8 (CH7), U9.14 (Out4)
/CE0: J4.24, U5.10 (~CS~/SHDN)
/InvFwd: TP1.1, U6.19 (1~OE), U10.6
/InvRev: TP2.1, U7.19 (1~OE), U10.4
/MISO: J4.21, U5.12 (Dout)
/MOSI: J4.19, U5.11 (Din)
/Mot1En: J4.36, Q2.1 (G), U6.2 (A1), U7.9 (A8)
/Mot1Fwd: U1.14 (AIN1), U6.18 (B1)
/Mot1Rev: U1.13 (AIN2), U7.11 (B8)
/Mot1SH: R5.1, U1.16 (AOUT1), U8.3 (In+1)
/Mot1SL: J5.12, R5.2, U8.2 (In-1)
/Mot1b: J5.5, U1.2 (AOUT2)
/Mot2En: J4.38, Q3.1 (G), U6.3 (A2), U7.8 (A7)
/Mot2Fwd: TP3.1, U1.7 (BIN1), U6.17 (B2)
/Mot2Rev: TP4.1, U1.8 (BIN2), U7.12 (B7)
/Mot2SH: R9.2, U1.5 (BOUT1), U8.5 (In+2)
/Mot2SL: J5.11, R9.1, U8.6 (In-2)
/Mot2b: J5.17, U1.3 (BOUT2)
/Mot3En: J4.40, Q4.1 (G), U6.4 (A3), U7.7 (A6)
/Mot3Fwd: U2.14 (AIN1), U6.16 (B3)
/Mot3Rev: U2.13 (AIN2), U7.13 (B6)
/Mot3SH: R6.1, U2.16 (AOUT1), U8.10 (In+3)
/Mot3SL: J5.1, R6.2, U8.9 (In-3)
/Mot3b: J5.2, U2.2 (AOUT2)
/Mot4En: J4.37, Q5.1 (G), U6.5 (A4), U7.6 (A5)
/Mot4Fwd: U2.7 (BIN1), U6.15 (B4)
/Mot4Rev: U2.8 (BIN2), U7.14 (B5)
/Mot4SH: R10.2, U2.5 (BOUT1), U8.12 (In+4)
/Mot4SL: J5.7, R10.1, U8.13 (In-4)
/Mot4b: J5.6, U2.3 (BOUT2)
/Mot5En: J4.35, Q12.1 (G), U6.6 (A5), U7.5 (A4)
/Mot5Fwd: U3.14 (AIN1), U6.14 (B5)
/Mot5Rev: U3.13 (AIN2), U7.15 (B4)
/Mot5SH: R7.1, U3.16 (AOUT1), U9.3 (In+1)
/Mot5SL: J5.9, R7.2, U9.2 (In-1)
/Mot5b: J5.8, U3.2 (AOUT2)
/Mot6En: J4.31, Q13.1 (G), U6.7 (A6), U7.4 (A3)
/Mot6Fwd: U3.7 (BIN1), U6.13 (B6)
/Mot6Rev: U3.8 (BIN2), U7.16 (B3)
/Mot6SH: R11.2, U3.5 (BOUT1), U9.5 (In+2)
/Mot6SL: J5.3, R11.1, U9.6 (In-2)
/Mot6b: J5.4, U3.3 (BOUT2)
/Mot7En: J4.29, Q14.1 (G), U6.8 (A7), U7.3 (A2)
/Mot7Fwd: U4.14 (AIN1), U6.12 (B7)
/Mot7Rev: U4.13 (AIN2), U7.17 (B2)
/Mot7SH: R8.1, U4.16 (AOUT1), U9.10 (In+3)
/Mot7SL: J5.20, R8.2, U9.9 (In-3)
/Mot7b: J5.16, U4.2 (AOUT2)
/Mot8En: J4.27, Q15.1 (G), U6.9 (A8), U7.2 (A1)
/Mot8Fwd: U4.7 (BIN1), U6.11 (B8)
/Mot8Rev: U4.8 (BIN2), U7.18 (B1)
/Mot8SH: R12.2, U4.5 (BOUT1), U9.12 (In+4)
/Mot8SL: J5.10, R12.1, U9.13 (In-4)
/Mot8b: J5.15, U4.3 (BOUT2)
/PauseLedB: J4.10, Q17.1 (G)
/PauseLedG: J4.12, Q7.1 (G)
/PauseLedR: J4.8, Q9.1 (G)
/PauseMosB: J9.6, Q17.3 (D)
/PauseMosG: J9.4, Q7.3 (D)
/PauseMosR: J9.5, Q9.3 (D)
/PauseOut: D9.2 (A), J9.3, Q11.1 (G)
/PauseRead: J4.16, R34.1
/PwmFwd: J4.33, U10.1
/PwmRev: J4.32, U10.3
/RunLedB: J4.17, Q16.1 (G)
/RunLedG: J4.13, Q6.1 (G)
/RunLedR: J4.15, Q8.1 (G)
/RunMosB: J8.6, Q16.3 (D)
/RunMosG: J8.4, Q6.3 (D)
/RunMosR: J8.5, Q8.3 (D)
/RunOut: D8.2 (A), J8.3, Q10.1 (G)
/RunRead: J4.18, R33.1
/SCL: J4.5, U13.4 (A2)
/SCLK: J4.23, U5.13 (CLK)
/SDA: J4.3, U13.5 (A1)
/SolSet: J4.11, Q1.1 (G)
/ToggleRead: J4.22, J7.1
GND: C1.2, C2.2, C3.2, C4.2, C5.2, C6.2, C7.2, C8.2, C13.2, C14.2, C15.2, C16.2, C17.2, C20.2, C21.2, C23.2, C25.2, C26.2, C27.2, C30.2, C31.1, J1.4, J2.1, J4.6, J4.9, J4.14, J4.20, J4.25, J4.30, J4.34, J4.39, J5.13, J5.14, J5.18, J5.19, J6.4, J8.7, J8.8, J9.7, J9.8, Q1.2 (S), Q2.2 (S), Q3.2 (S), Q4.2 (S), Q5.2 (S), Q6.2 (S), Q7.2 (S), Q8.2 (S), Q9.2 (S), Q10.2 (S), Q11.2 (S), Q12.2 (S), Q13.2 (S), Q14.2 (S), Q15.2 (S), Q16.2 (S), Q17.2 (S), R13.2, R16.2, R28.1, R29.1, R30.1, R31.1, R40.2, R42.2, U1.1 (AISEN), U1.4 (BISEN), U1.11 (GND), U1.17 (GND(PPAD)), U2.1 (AISEN), U2.4 (BISEN), U2.11 (GND), U2.17 (GND(PPAD)), U3.1 (AISEN), U3.4 (BISEN), U3.11 (GND), U3.17 (GND(PPAD)), U4.1 (AISEN), U4.4 (BISEN), U4.11 (GND), U4.17 (GND(PPAD)), U5.9 (DGND), U5.14 (AGND), U6.10 (GND), U6.21 (GND(PPAD)), U7.10 (GND), U7.21 (GND(PPAD)), U8.11 (GND), U9.11 (GND), U10.2 (GND), U11.4 (GND), U11.9 (EP), U12.4 (GND), U12.9 (EP), U13.2 (GND)
unnamed: C1.1, U1.12 (VINT)
unnamed: C3.1, U2.12 (VINT)
unnamed: C5.1, U3.12 (VINT)
unnamed: C7.1, U4.12 (VINT)
unnamed: C9.1, U1.9 (VCP)
unnamed: C10.1, U2.9 (VCP)
unnamed: C11.1, U3.9 (VCP)
unnamed: C12.1, U4.9 (VCP)
unnamed: C18.1, L1.1, U11.3 (SW)
unnamed: C18.2, U11.1 (BST)
unnamed: C19.1, L2.1, U12.3 (SW)
unnamed: C19.2, U12.1 (BST)
unnamed: C22.1, R28.2
unnamed: C22.2, U11.6 (COMP)
unnamed: C24.1, R30.2
unnamed: C24.2, U12.6 (COMP)
unnamed: C26.1, U11.8 (SS)
unnamed: C27.1, U12.8 (SS)
unnamed: D1.1 (K), R13.1
unnamed: D2.1 (K), D3.2 (A), J3.2, Q1.3 (D)
unnamed: D2.2 (A), R15.2
unnamed: D4.1 (K), Q2.3 (D)
unnamed: D4.2 (A), R23.2
unnamed: D5.1 (K), Q3.3 (D)
unnamed: D5.2 (A), R14.2
unnamed: D6.1 (K), Q4.3 (D)
unnamed: D6.2 (A), R17.2
unnamed: D7.1 (K), Q5.3 (D)
unnamed: D7.2 (A), R18.2
unnamed: D8.1 (K), R40.1
unnamed: D9.1 (K), R42.1
unnamed: D10.1 (K), Q12.3 (D)
unnamed: D10.2 (A), R19.2
unnamed: D11.1 (K), Q13.3 (D)
unnamed: D11.2 (A), R20.2
unnamed: D12.1 (K), Q14.3 (D)
unnamed: D12.2 (A), R21.2
unnamed: D13.1 (K), Q15.3 (D)
unnamed: D13.2 (A), R22.2
unnamed: J1.2, J6.2, U13.8 (B1)
unnamed: J1.3, J6.3, U13.1 (B2)
unnamed: J7.2, R16.1
unnamed: Q10.3 (D), R33.2
unnamed: Q11.3 (D), R34.2
unnamed: R1.1, U1.15 (nSLEEP)
unnamed: R2.1, U2.15 (nSLEEP)
unnamed: R3.1, U3.15 (nSLEEP)
unnamed: R4.1, U4.15 (nSLEEP)
unnamed: R24.2, U11.7 (EN)
unnamed: R25.2, U12.7 (EN)
unnamed: R26.1, R29.2, U11.5 (FB)
unnamed: R27.1, R31.2, U12.5 (FB)
unnamed: R32.1, U13.6 (OE)

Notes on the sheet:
DC Motor Drivers
12V Supply
PWM Inverters
I2C Motor Connectors
Pause Switch
Run Switch
DC Motor Enable Indicator LEDs
Current Monitors
ADC
DC Driver Inputs
Solenoid
Toggle Switch
10V Power Regulator
5V Power Regulator
Pi Header
Head Unit Connector
DC Motor Components
Power Regulation
Bulk Connectors
Peripherals

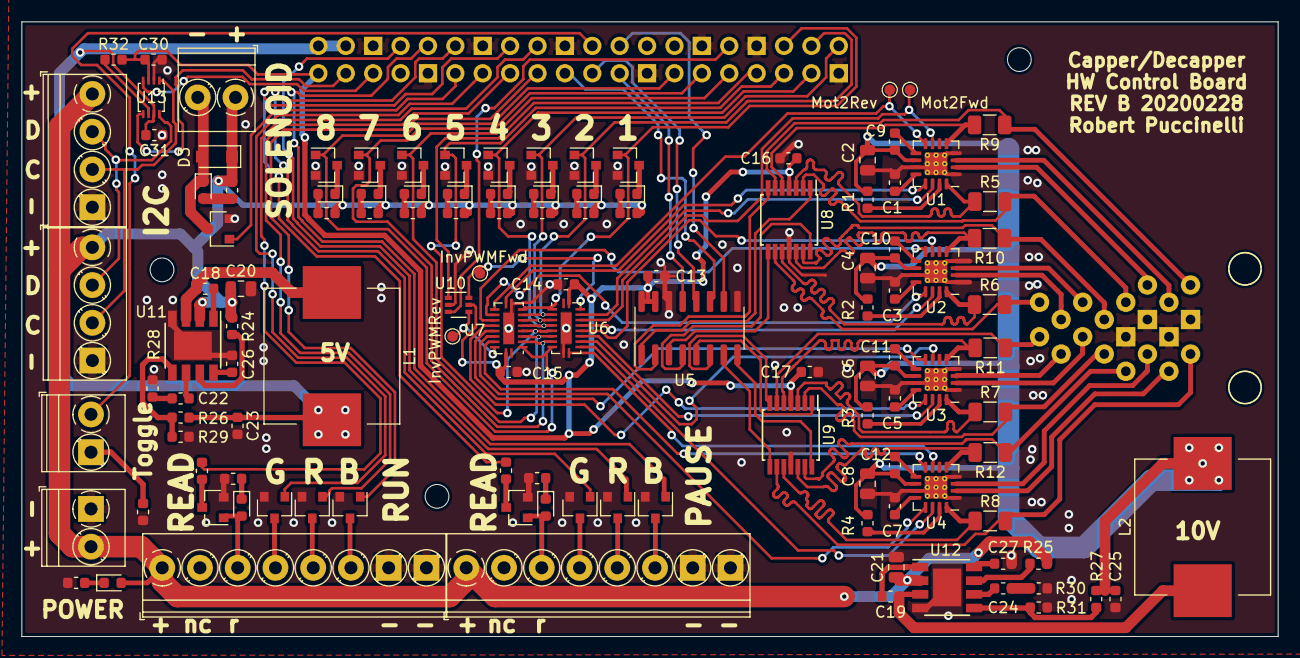
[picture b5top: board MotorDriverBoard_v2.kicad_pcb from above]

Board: 2 copper layers, 116.5 x 57.0 mm, 126 parts (1 on the bottom side), 142 nets.
